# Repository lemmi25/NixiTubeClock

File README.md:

# ESP32 NixiTube OTA Clock

## Hardware Profiles

Firmware variants live in src/hardware:

- master_no_rtc.cpp
	- No RTC module
	- Time sync from internet API
	- FreeRTOS tasks (display/buttons and WiFi/OTA)
- rtc_local.cpp
	- DS1307 RTC module
	- Local time from RTC with optional internet sync
	- Power and menu button handling in single-loop runtime

## Tube Types

Tube mapping is selected in include/clock_variant_config.h via config.env:

- ZM1000
- IN4
- DA2000 (numitron)

## Main Configuration

All build-time options are read from config.env by extra_scripts/read_config_env.py.
Each key in config.env becomes a C/C++ define automatically.

Typical minimal setup:

```env
HARDWARE_PROFILE=RTC_LOCAL
TUBE_TYPE=ZM1000

ENABLE_OTA=1
OTA_IP=192.168.10.56
OTA_PASSWORD=nixiclock

WIFI_SSID=YOUR_WIFI_SSID
WIFI_PASSWORD=YOUR_WIFI_PASSWORD
CITY=Europe/Berlin
TIME_API_BASE=https://timeapi.io/api/Time/current/zone?timeZone=
```

## OTA Update

OTA is enabled with ENABLE_OTA=1.

- OTA stays always available after WiFi is connected.
- Flash command:

```bash
./scripts/ota_flash_monitor.sh
```

The script reads OTA_IP, OTA_PASSWORD, OTA_PORT from config.env, builds firmware, uploads over OTA, then opens serial monitor.

## Buttons And LEDs

Current runtime behavior:

- Power button (BTN_ON / GPIO3): toggle hibernate and wake
- Menu button (BTN_MODE / GPIO15): short/long press function handling
- LED brightness level: LED_DIM
	- master_no_rtc currently uses LED_DIM in firmware defaults
	- rtc_local supports LED_DIM from config.env and includes boot LED intro animation

## Build

USB build/upload:

```bash
platformio run -e esp-wrover-kit
```

OTA build/upload environment:

```bash
platformio run -e esp-wrover-kit-ota
```

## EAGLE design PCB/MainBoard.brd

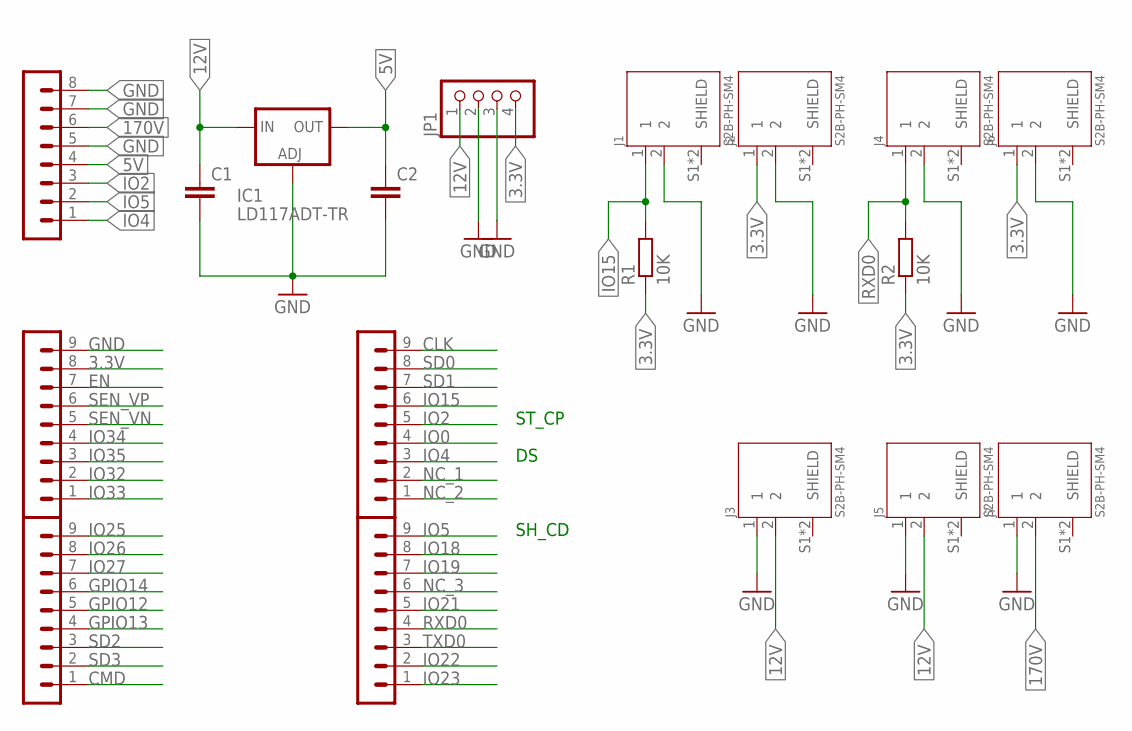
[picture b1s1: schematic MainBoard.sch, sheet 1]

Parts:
C1, C2: C-EU_1206C1206; C1206
IC1: LD117ADT-TR; DPACK
J1, J2, J3, J4, J5, J6, J7: S2B-PH-SM4; JST_S2B-PH-SM4-TB(LF)(SN)
JP1: PINHD-1X4; 1X04
R1, R2: 10K; R1206
SV1: PINHEADER-1X8; MA08-1
SV2, SV3, SV4, SV5: PINHEADER-1X9; MA09-1

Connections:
3.3V: J2.1, J6.1, JP1.4, R1.1, R2.1, SV2.8
5V: C2.1, IC1.4 (OUT), SV1.4
12V: C1.1, IC1.3 (IN), J3.2, J5.2, JP1.1
170V: J7.2, SV1.6
CLK: SV4.9
CMD: SV3.1
EN: SV2.7
GND: C1.2, C2.2, IC1.1 (ADJ), J1.2, J2.2, J3.1, J4.2, J5.1, J6.2, J7.1, JP1.2, JP1.3, SV1.5, SV1.7, SV1.8, SV2.9
GPIO12: SV3.5
GPIO13: SV3.4
GPIO14: SV3.6
IO0: SV4.4
IO2: SV1.3, SV4.5
IO4: SV1.1, SV4.3
IO5: SV1.2, SV5.9
IO15: J1.1, R1.2, SV4.6
IO18: SV5.8
IO19: SV5.7
IO21: SV5.5
IO22: SV5.2
IO23: SV5.1
IO25: SV3.9
IO26: SV3.8
IO27: SV3.7
IO32: SV2.2
IO33: SV2.1
IO34: SV2.4
IO35: SV2.3
NC_1: SV4.2
NC_2: SV4.1
NC_3: SV5.6
RXD0: J4.1, R2.2, SV5.4
SD0: SV4.8
SD1: SV4.7
SD2: SV3.3
SD3: SV3.2
SEN_VN: SV2.5
SEN_VP: SV2.6
TXD0: SV5.3

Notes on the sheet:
ST_CP
SH_CD

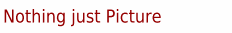
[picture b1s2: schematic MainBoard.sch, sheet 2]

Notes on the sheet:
Nothing just Picture

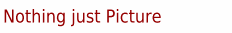
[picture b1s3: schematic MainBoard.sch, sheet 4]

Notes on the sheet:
Nothing just Picture

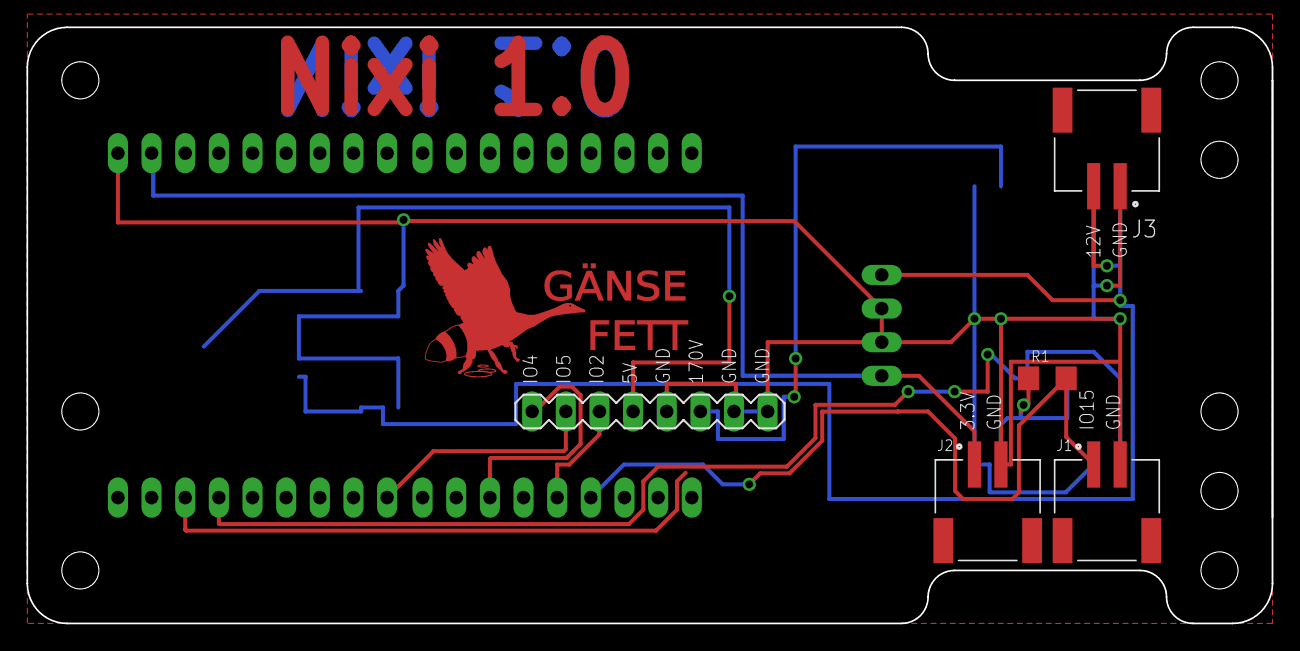
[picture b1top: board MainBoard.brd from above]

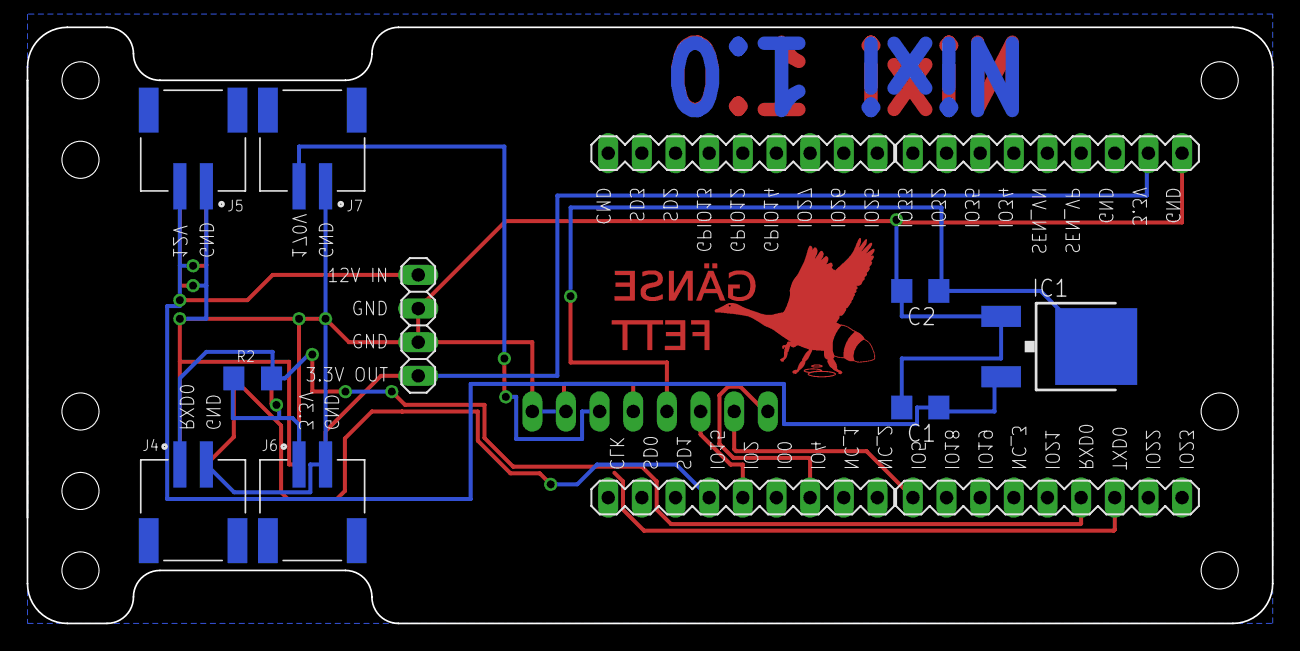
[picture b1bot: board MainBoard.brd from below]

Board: 2 copper layers, 94.0 x 45.0 mm, 18 parts (13 on the bottom side), 10 nets.

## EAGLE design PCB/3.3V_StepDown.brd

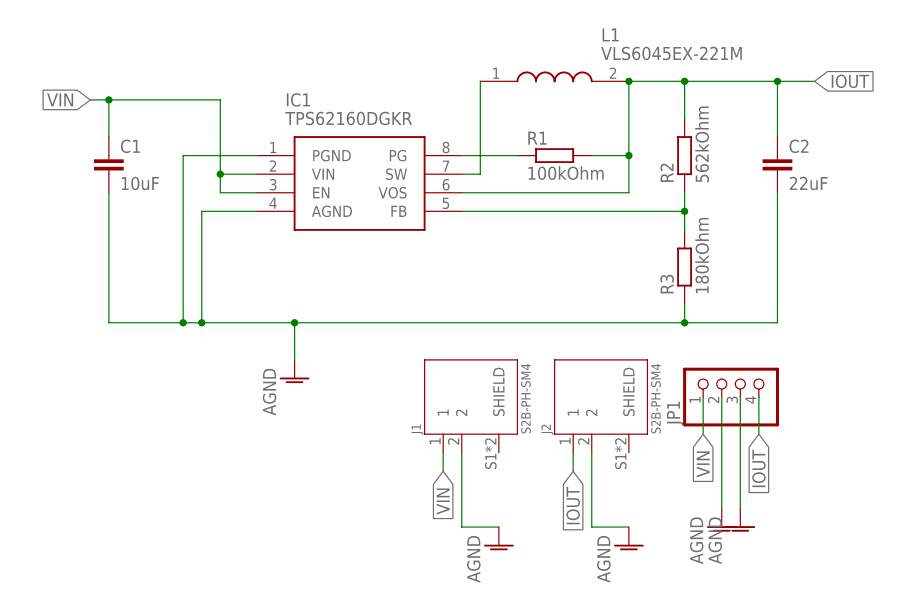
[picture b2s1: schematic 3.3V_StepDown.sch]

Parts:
C1: 10uF; C1206
C2: 22uF; C0805K
IC1: TPS62160DGKR; SOP65P490X110-8N
J1, J2: S2B-PH-SM4; JST_S2B-PH-SM4-TB(LF)(SN)
JP1: PINHD-1X4; 1X04
L1: VLS6045EX-221M; INDPM6060X450N
R1: 100kOhm; R1206
R2: 562kOhm; R0805
R3: 180kOhm; R0402

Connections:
AGND: C1.2, C2.2, IC1.1 (PGND), IC1.4 (AGND), J1.2, J2.2, JP1.2, JP1.3, R3.1
FB2: IC1.5 (FB), R2.1, R3.2
IOUT: C2.1, IC1.6 (VOS), J2.1, JP1.4, L1.2, R1.2, R2.2
PG2: IC1.8 (PG), R1.1
SW2: IC1.7 (SW), L1.1
VIN: C1.1, IC1.2 (VIN), IC1.3 (EN), J1.1, JP1.1

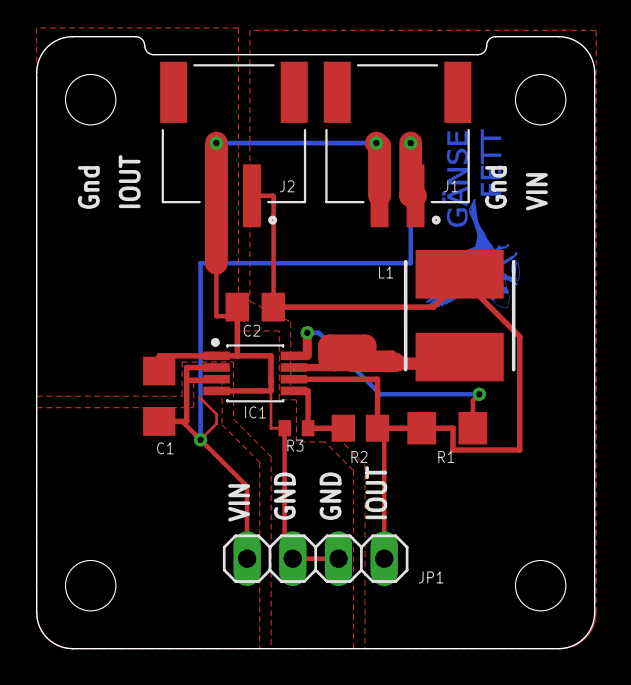
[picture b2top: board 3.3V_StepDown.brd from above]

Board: 2 copper layers, 31.0 x 34.0 mm, 10 parts (0 on the bottom side), 6 nets.

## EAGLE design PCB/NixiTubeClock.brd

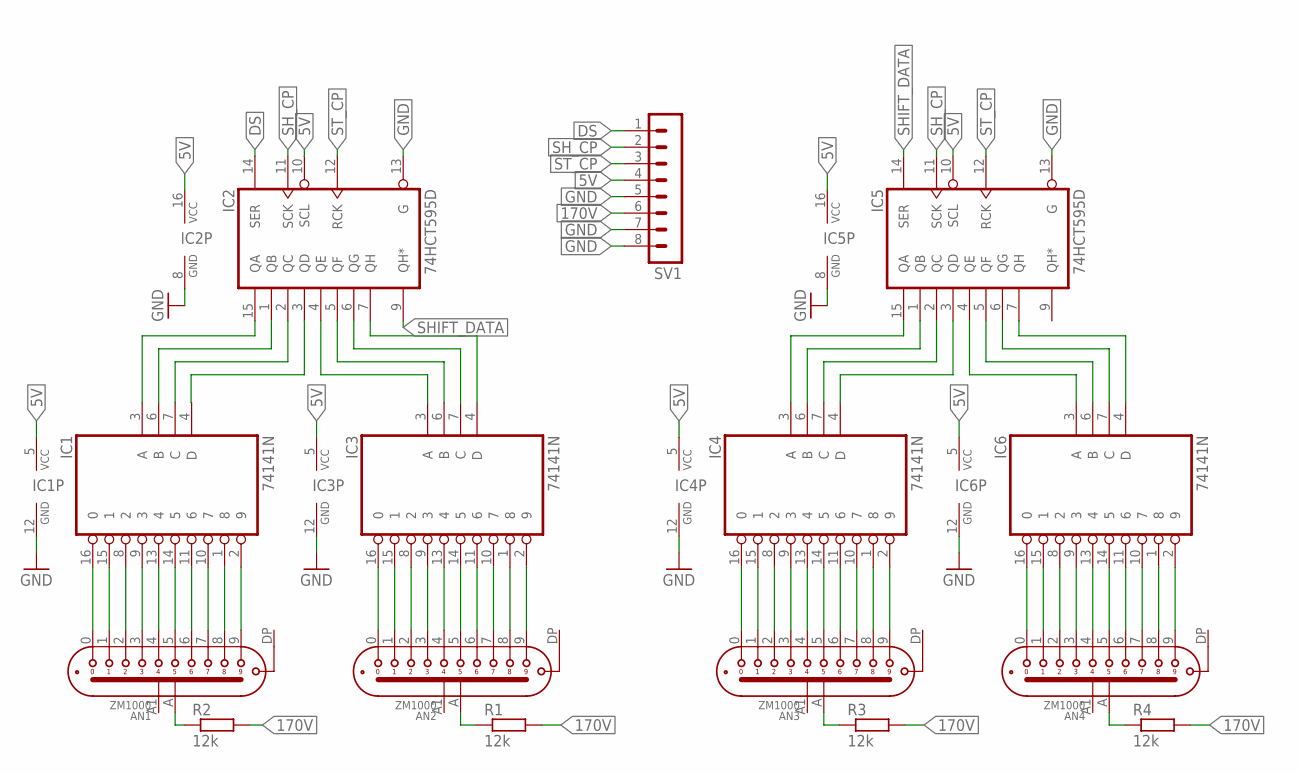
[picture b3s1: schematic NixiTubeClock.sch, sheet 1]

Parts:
AN1, AN2, AN3, AN4: ZM1000
IC1, IC3, IC4, IC6: 74141N; DIL16
IC2, IC5: 74HCT595D; SO16
R1, R2, R3, R4: 12k; R1206
SV1: MA08-1

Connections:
5V: IC1.5 (VCC), IC2.10 (SCL), IC2.16 (VCC), IC3.5 (VCC), IC4.5 (VCC), IC5.10 (SCL), IC5.16 (VCC), IC6.5 (VCC), SV1.4
170V: R1.2, R2.2, R3.2, R4.2, SV1.6
DS: IC2.14 (SER), SV1.1
GND: IC1.12 (GND), IC2.8 (GND), IC2.13 (G), IC3.12 (GND), IC4.12 (GND), IC5.8 (GND), IC5.13 (G), IC6.12 (GND), SV1.5, SV1.7, SV1.8
unnamed: IC4.4 (D), IC5.3 (QD)
unnamed: AN1.0, IC1.16 (0)
unnamed: AN1.1, IC1.15 (1)
unnamed: AN1.2, IC1.8 (2)
unnamed: AN1.3, IC1.9 (3)
unnamed: AN1.4, IC1.13 (4)
unnamed: AN1.5, IC1.14 (5)
unnamed: AN1.6, IC1.11 (6)
unnamed: AN1.7, IC1.10 (7)
unnamed: AN1.8, IC1.1 (8)
unnamed: AN1.9, IC1.2 (9)
unnamed: AN2.0, IC3.16 (0)
unnamed: AN2.1, IC3.15 (1)
unnamed: AN2.2, IC3.8 (2)
unnamed: AN2.3, IC3.9 (3)
unnamed: AN2.4, IC3.13 (4)
unnamed: AN2.5, IC3.14 (5)
unnamed: AN2.6, IC3.11 (6)
unnamed: AN2.7, IC3.10 (7)
unnamed: AN2.8, IC3.1 (8)
unnamed: AN2.9, IC3.2 (9)
unnamed: AN3.0, IC4.16 (0)
unnamed: AN3.1, IC4.15 (1)
unnamed: AN3.2, IC4.8 (2)
unnamed: AN3.3, IC4.9 (3)
unnamed: AN3.4, IC4.13 (4)
unnamed: AN3.5, IC4.14 (5)
unnamed: AN3.6, IC4.11 (6)
unnamed: AN3.7, IC4.10 (7)
unnamed: AN3.8, IC4.1 (8)
unnamed: AN3.9, IC4.2 (9)
unnamed: AN4.0, IC6.16 (0)
unnamed: AN4.1, IC6.15 (1)
unnamed: AN4.2, IC6.8 (2)
unnamed: AN4.3, IC6.9 (3)
unnamed: AN4.4, IC6.13 (4)
unnamed: AN4.5, IC6.14 (5)
unnamed: AN4.6, IC6.11 (6)
unnamed: AN4.7, IC6.10 (7)
unnamed: AN4.8, IC6.1 (8)
unnamed: AN4.9, IC6.2 (9)
unnamed: AN1.A (A1), R2.1
unnamed: AN2.A (A1), R1.1
unnamed: AN3.A (A1), R3.1
unnamed: AN4.A (A1), R4.1
unnamed: IC1.3 (A), IC2.15 (QA)
unnamed: IC1.6 (B), IC2.1 (QB)
unnamed: IC1.7 (C), IC2.2 (QC)
unnamed: IC1.4 (D), IC2.3 (QD)
unnamed: IC2.4 (QE), IC3.3 (A)
unnamed: IC2.5 (QF), IC3.6 (B)
unnamed: IC2.6 (QG), IC3.7 (C)
unnamed: IC2.7 (QH), IC3.4 (D)
unnamed: IC4.3 (A), IC5.15 (QA)
unnamed: IC4.6 (B), IC5.1 (QB)
unnamed: IC4.7 (C), IC5.2 (QC)
unnamed: IC5.4 (QE), IC6.3 (A)
unnamed: IC5.5 (QF), IC6.6 (B)
unnamed: IC5.6 (QG), IC6.7 (C)
unnamed: IC5.7 (QH), IC6.4 (D)
SHIFT_DATA: IC2.9 (QH*), IC5.14 (SER)
SH_CP: IC2.11 (SCK), IC5.11 (SCK), SV1.2
ST_CP: IC2.12 (RCK), IC5.12 (RCK), SV1.3

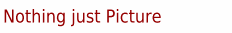
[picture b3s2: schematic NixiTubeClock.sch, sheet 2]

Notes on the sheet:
Nothing just Picture

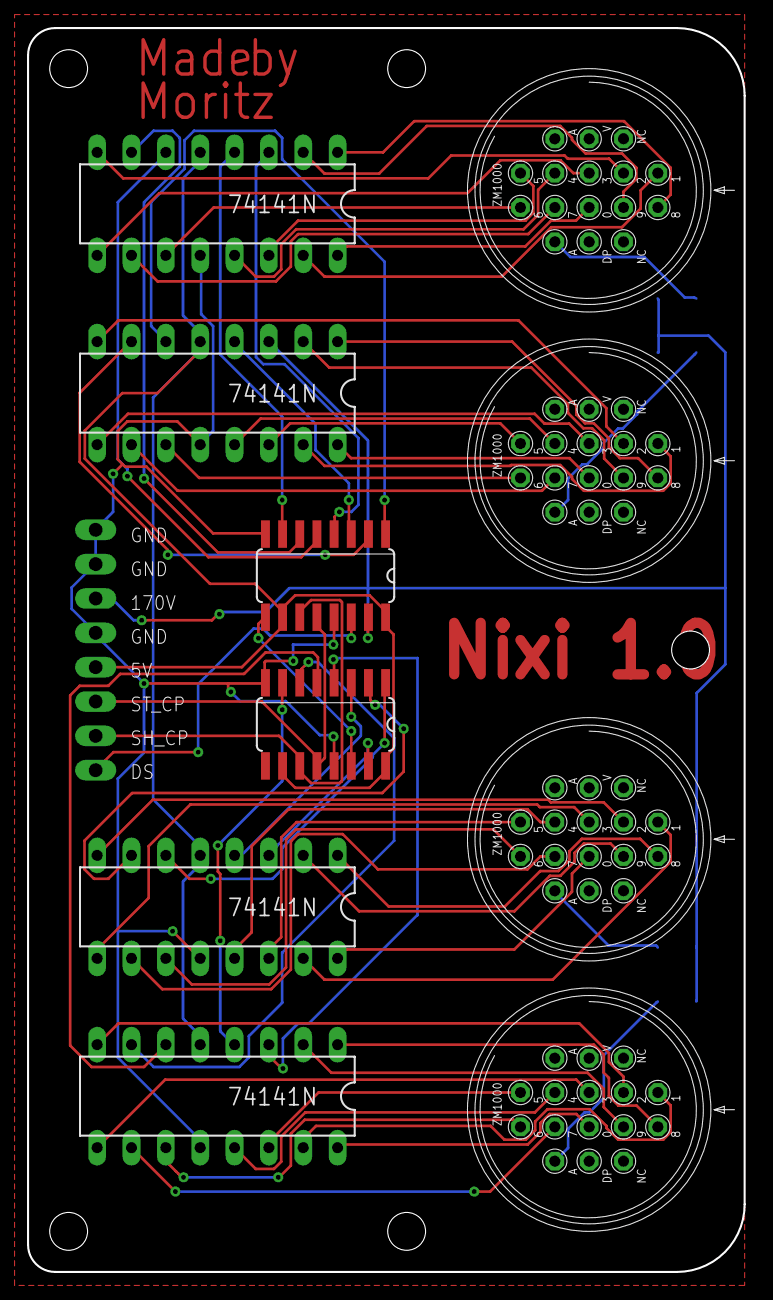
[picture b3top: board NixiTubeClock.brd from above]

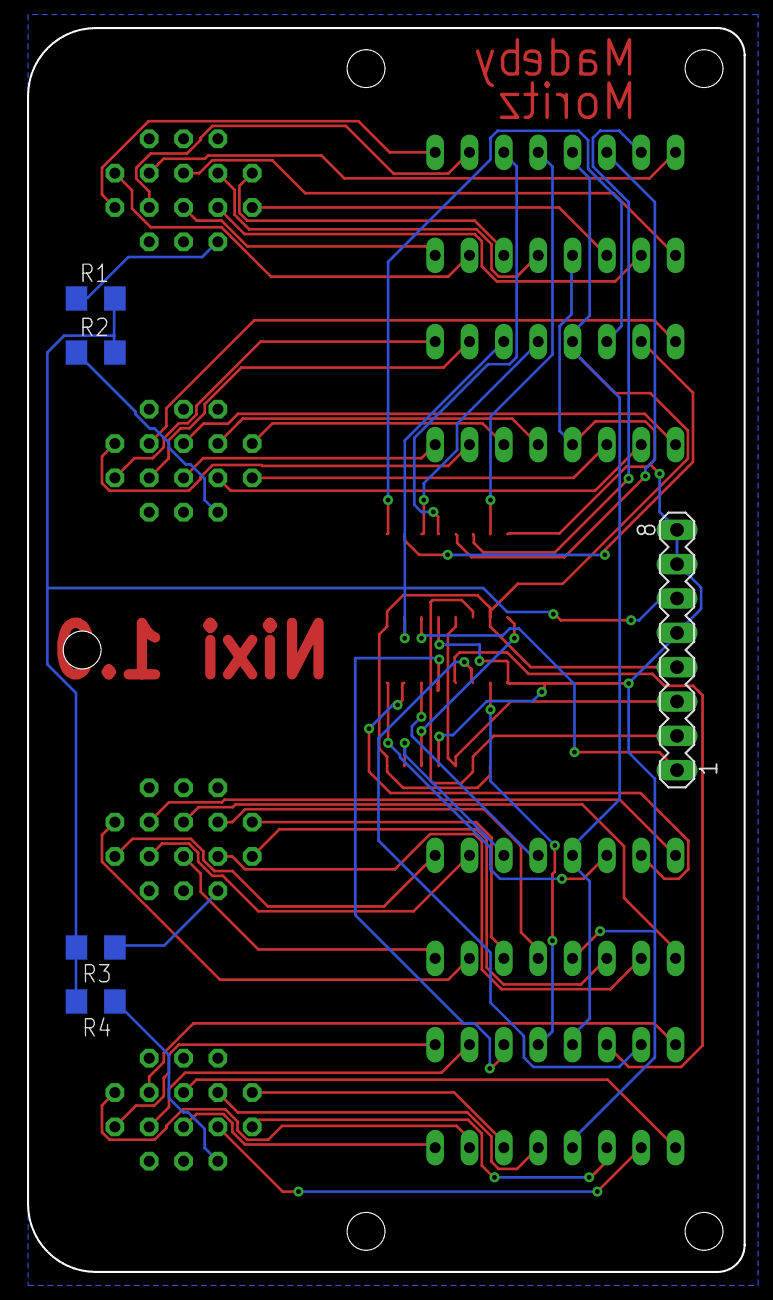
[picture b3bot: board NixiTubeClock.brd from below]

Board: 2 copper layers, 53.0 x 92.0 mm, 15 parts (5 on the bottom side), 67 nets.

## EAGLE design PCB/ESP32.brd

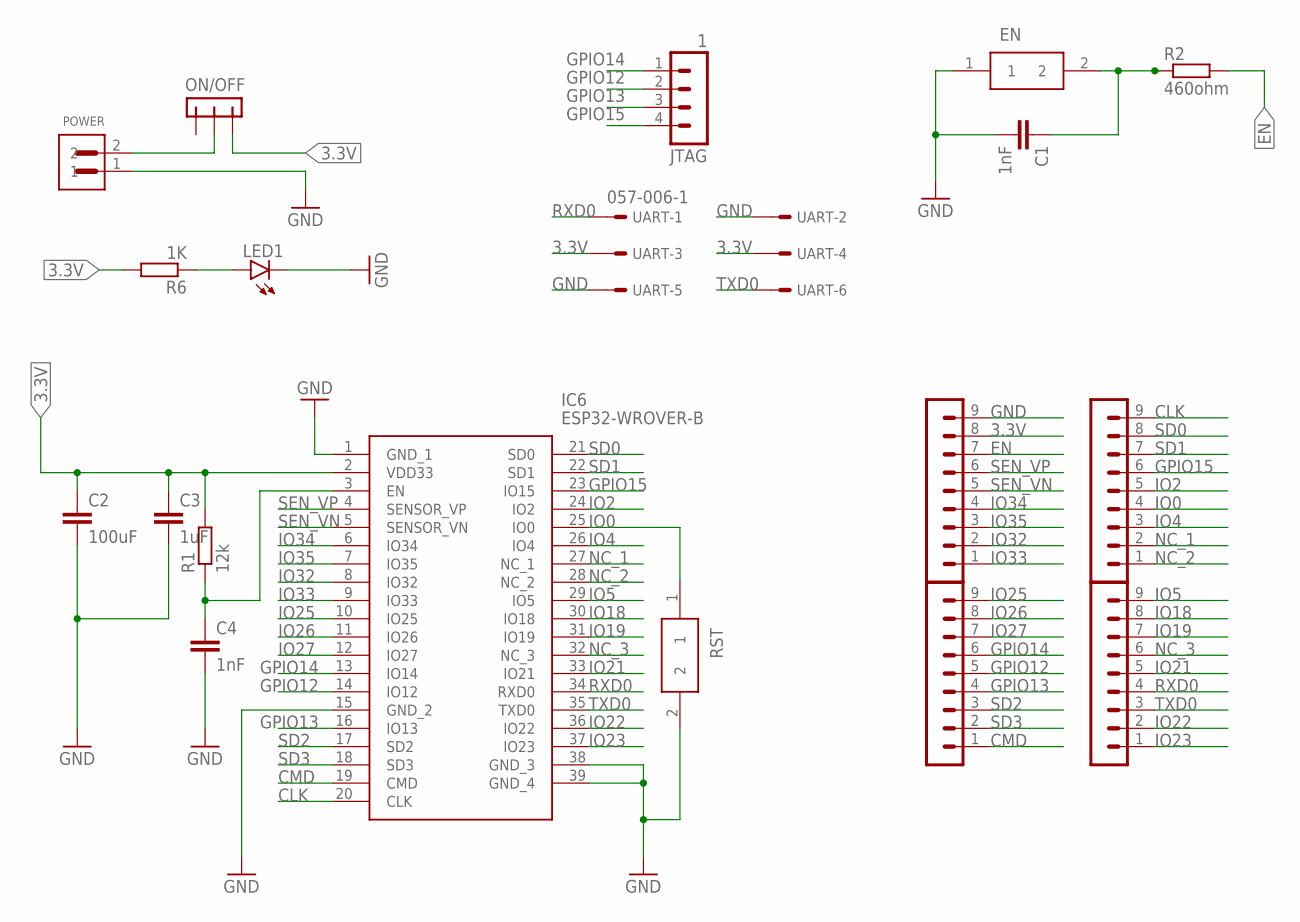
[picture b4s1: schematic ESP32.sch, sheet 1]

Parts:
C1, C4: 1nF; C0805
C2: 100uF; C1206
C3: 1uF; C0805
EN: FSMSMTR; FSMSM
IC6: ESP32-WROVER-B; ESP32WROVERIB16MB
JTAG: 1; MA04-1
LED1: LEDSMT1206; 1206
ON/OFF: -CON3; CON3
POWER: S2B-PH-SM4-TB; JST_S2B-PH-SM4-TB
R1: 12k; R0805
R2: 460ohm; R0805
R6: 1K; R1206
RST: FSMSMTR; FSMSM
SV1, SV2, SV5, SV6: PINHEADER-1X9; MA09-1
UART: 057-006-1

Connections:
3.3V: C2.1, C3.1, IC6.2 (VDD33), ON/OFF.P$1 (1), R1.2, R6.2, SV5.8, UART.3, UART.4
CLK: IC6.20 (CLK), SV1.9
CMD: IC6.19 (CMD), SV6.1
EN: C1.1, C4.1, EN.2, IC6.3 (EN), R1.1, R2.1, R2.2, SV5.7
GND: C1.2, C2.2, C3.2, C4.2, EN.1, IC6.1 (GND_1), IC6.15 (GND_2), IC6.38 (GND_3), IC6.39 (GND_4), LED1.C, POWER.1, RST.2, SV5.9, UART.2, UART.5
GPIO12: IC6.14 (IO12), JTAG.2, SV6.5
GPIO13: IC6.16 (IO13), JTAG.3, SV6.4
GPIO14: IC6.13 (IO14), JTAG.1, SV6.6
GPIO15: IC6.23 (IO15), JTAG.4, SV1.6
IO0: IC6.25 (IO0), RST.1, SV1.4
IO2: IC6.24 (IO2), SV1.5
IO4: IC6.26 (IO4), SV1.3
IO5: IC6.29 (IO5), SV2.9
IO18: IC6.30 (IO18), SV2.8
IO19: IC6.31 (IO19), SV2.7
IO21: IC6.33 (IO21), SV2.5
IO22: IC6.36 (IO22), SV2.2
IO23: IC6.37 (IO23), SV2.1
IO25: IC6.10 (IO25), SV6.9
IO26: IC6.11 (IO26), SV6.8
IO27: IC6.12 (IO27), SV6.7
IO32: IC6.8 (IO32), SV5.2
IO33: IC6.9 (IO33), SV5.1
IO34: IC6.6 (IO34), SV5.4
IO35: IC6.7 (IO35), SV5.3
unnamed: ON/OFF.P$2 (2), POWER.2
unnamed: LED1.A, R6.1
NC_1: IC6.27 (NC_1), SV1.2
NC_2: IC6.28 (NC_2), SV1.1
NC_3: IC6.32 (NC_3), SV2.6
RXD0: IC6.34 (RXD0), SV2.4, UART.1
SD0: IC6.21 (SD0), SV1.8
SD1: IC6.22 (SD1), SV1.7
SD2: IC6.17 (SD2), SV6.3
SD3: IC6.18 (SD3), SV6.2
SEN_VN: IC6.5 (SENSOR_VN), SV5.5
SEN_VP: IC6.4 (SENSOR_VP), SV5.6
TXD0: IC6.35 (TXD0), SV2.3, UART.6

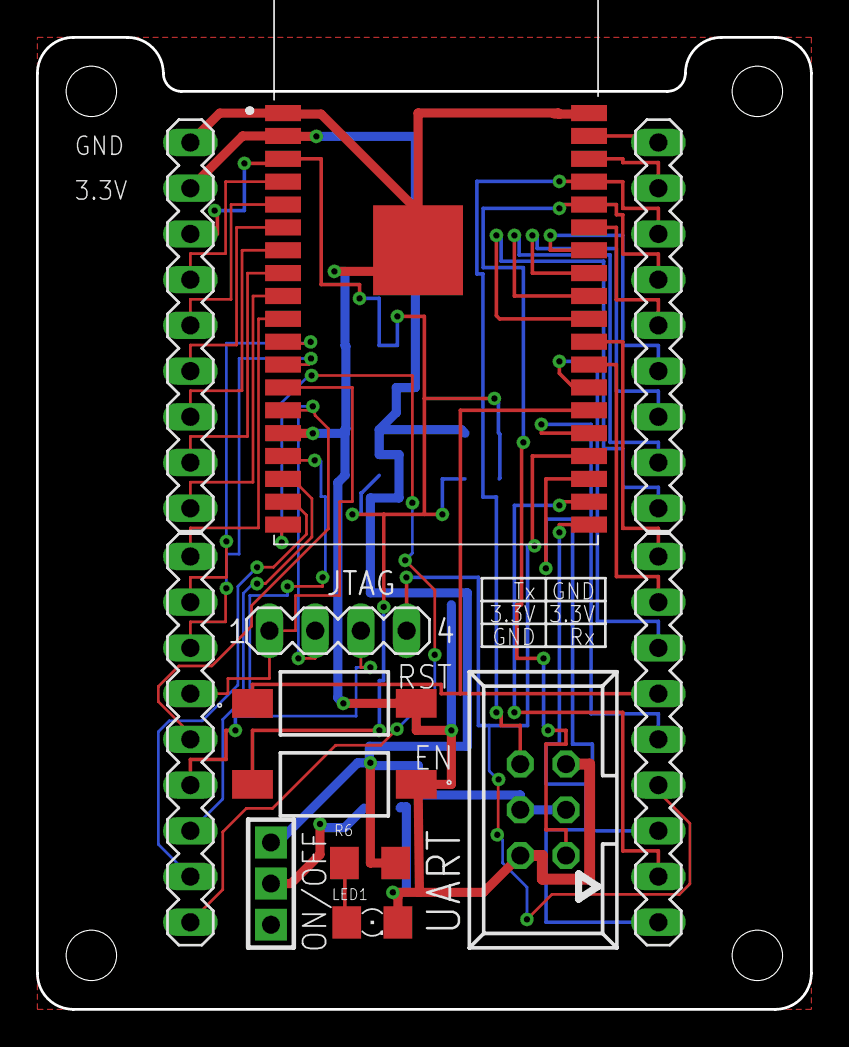
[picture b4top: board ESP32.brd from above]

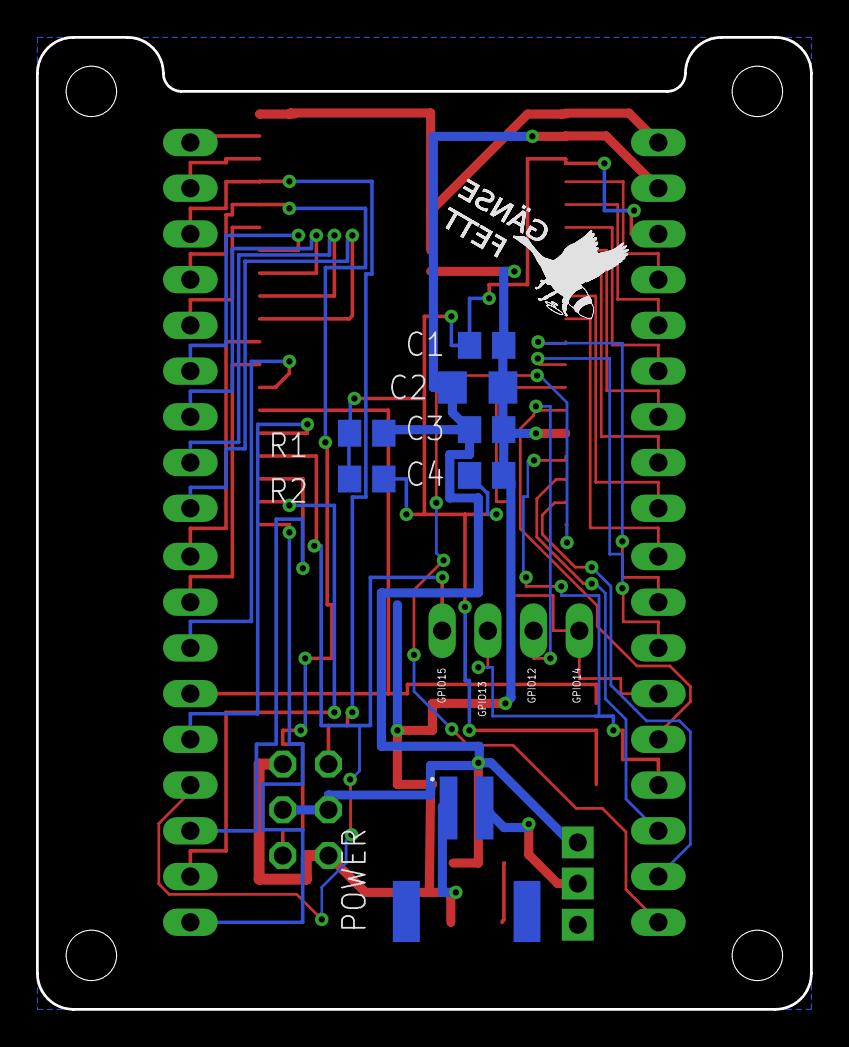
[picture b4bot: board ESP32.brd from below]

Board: 2 copper layers, 43.0 x 54.0 mm, 19 parts (7 on the bottom side), 38 nets.

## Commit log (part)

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2019-12-17 minor changes like free and timing in main
2019-12-22 fixed memorie leak
2019-12-23 added temperature from api
2019-12-23 added temp and hp
2019-12-23 minor parsing changes
2019-12-25 added correct ssid and psw
2019-12-25 added image
2019-12-26 enabled startup sequence and some comments
2019-12-28 correct temp and pres update
2019-12-30 correct 0 error on temp
2019-12-31 improved json
2020-01-12 added pcb
2020-01-16 added case Folder for lasercutter
2020-01-19 added RTC, SHT21, LED Pins support
2020-02-17 added buzzer
2020-03-23 started with rtos build up
2020-03-23 added start and on off
2020-03-25 added stop clock+
2020-03-26 added debouncing for stop clock start and end
2020-03-29 added all sensors and zm100 support
2020-03-29 added startup sequence
2020-04-06 added wifi update on time humidity and temp
2020-04-06 minor time change
2020-04-09 added changes to RTC
2020-04-12 changed wlan task to main loop is not an rtos task any more
2020-04-14 will show correct time now from beginning
2020-04-14 added changes for correct time show on startup
2020-04-14 changed rtc battery polarity ;D
2020-04-17 changed oo loop for wifi wait
2020-04-20 removed startup sequence
2020-06-27 added manual
2020-10-17 latest version from old ubuntu
2020-11-03 minor changes
2020-11-03 flash for iphone
2020-11-03 added seconds from internet api for more precise time
2021-01-09 fixed timimng update from internet problem
2021-01-11 added support for DA2000 numitron
2021-05-15 changes for no attached temp hum sensor
2022-09-25 changed time for better precision
2022-09-25 small changhe for printing
